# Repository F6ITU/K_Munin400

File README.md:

# K_Munin400
LA2NI's OpenHPSDR 400W HF amplifier (Kicad Version)

This amplifier board is part of a set consisting of a 400 W LD-Mos based RF power amplifier (Munin 400), 
a medium power Zolotarev low pass filter (600 or 1500 W), an Automatic Antenna Tuner (ATU) nickname « Aries » 
and a 4 port antenna switch.

All these developments are the work and intellectual property of Kjell Karlsen LA2NI and Laurence Barker G8NJJ.

This original work can be downloaded from

https://github.com/LA2NI/

https://github.com/laurencebarker

This board was originally developed in December 2021 by Kjell LA2NI , with UltiBoard EDA. This repository is a « bug for bug »
clone of the original amplifier using the Opensource Kicad EDA. 
All these KiCad files are, consequently, the intellectual property of Kjell LA2NI.

This portage (convertion/translation) is placed under the CERN Open source/ Open hardware Licence.

Kicad is an Opensource EDA software maintained by the European Reseach Center CERN (Conseil européen pour la recherche nucléaire)

The original work is protected by the TAPR Open Hardware licence

Munin and Hugin are the two "messenger" ravens of the Norse god Odin - just as Hermes is the messenger-god in Greek mythology, 
and the masterpiece of the OpenHPSDR architecture 

This LDMoS transistor-based amplifier brings speech over the great distances of the "Midgard" of the waves

# Work in progress
do NOT use these files as long as this footnote hasn't been deleted

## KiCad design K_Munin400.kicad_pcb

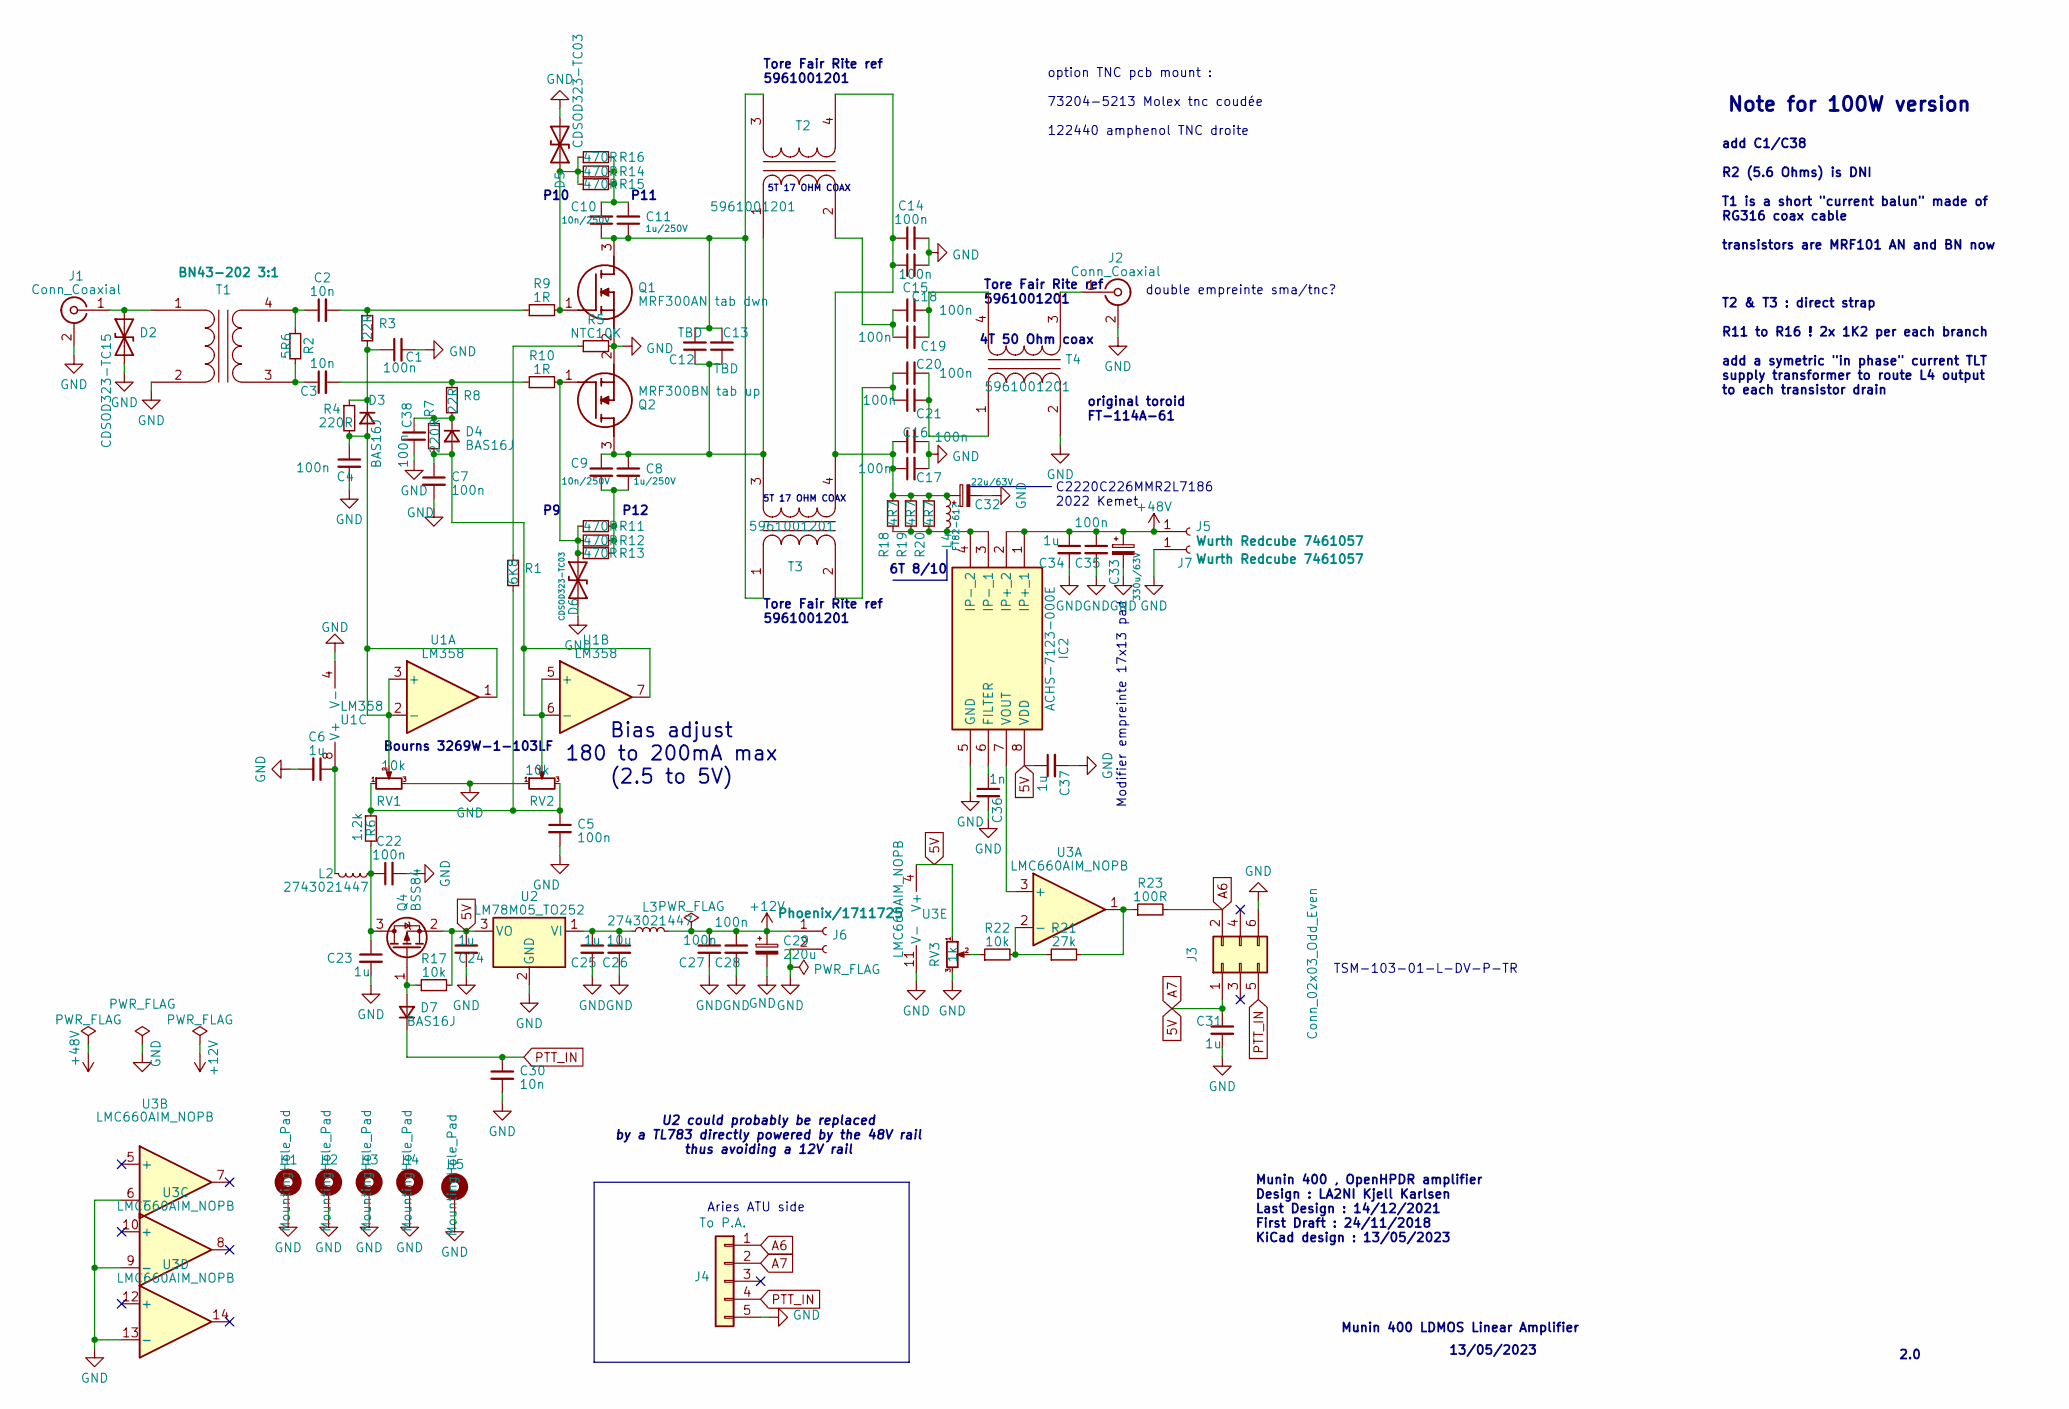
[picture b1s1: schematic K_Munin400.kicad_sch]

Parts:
C1, C38: 100n; C_0805_2012Metric
C2, C3, C30: 10n; C_0805_2012Metric_Pad1.18x1.45mm_HandSolder
C4, C5, C7, C22, C27, C28, C35: 100n; C_0805_2012Metric_Pad1.18x1.45mm_HandSolder
C6, C23, C24, C25, C31, C34, C37: 1u; C_0805_2012Metric_Pad1.18x1.45mm_HandSolder
C8, C11: 1u/250V; C_1812_4532Metric_Pad1.57x3.40mm_HandSolder
C9, C10: 10n/250V; C_1812_4532Metric_Pad1.57x3.40mm_HandSolder
C12, C13: TBD; C_1812_4532Metric_Pad1.57x3.40mm_HandSolder
C14, C15, C16, C17, C18, C19, C20, C21: 100n; C_1812_4532Metric_Pad1.57x3.40mm_HandSolder
C26: 10u; CP_EIA-7343-31_Kemet-D_Pad2.25x2.55mm_HandSolder
C29: 220u; C_Elec_8x10.2
C32: 22u/63V; C_2220_5650Metric_Pad1.97x5.40mm_HandSolder
C33: 330u/63V; CP_Elec_18x17.5
C36: 1n; C_0805_2012Metric_Pad1.18x1.45mm_HandSolder
D2: CDSOD323-TC15; D_SOD-323_HandSoldering
D3, D4, D7: BAS16J; D_SOD-323_HandSoldering
D5, D6: CDSOD323-TC03; D_SOD-323_HandSoldering
H1, H2, H3, H4, H5: MountingHole_Pad; MountingHole_3.5mm_Pad_TopBottom
IC2: ACHS-7123-000E; SOIC-8_3.9x4.9mm_P1.27mm; Mouser Part Number 630-ACHS-7123-000E
J1, J2: Conn_Coaxial; SMA_PINS
J3: Conn_02x03_Odd_Even; IDC-Header_2x03_P2.54mm_Vertical_SMD
J4: To P.A.; Molex_KK-254_AE-6410-05A_1x05_P2.54mm_Vertical
J5, J7: Wurth Redcube 7461057; 7461057
J6: Phoenix/1711725; 1711725
L2, L3: 2743021447; Fair-Rite_2743021447
L4: FT82-61?; T50_V_smd
Q1: MRF300AN tab dwn; TO-247-3_Horizontal_TabDown; Mouser Part Number 771-MRF300AN
Q2: MRF300BN tab up; TO-247-3_Horizontal_TabUp; Mouser Part Number 771-MRF300AN
Q4: BSS84; SOT-23
R1: 6K8; R_0805_2012Metric_Pad1.20x1.40mm_HandSolder
R2: 5R6; R_1812_4532Metric_Pad1.30x3.40mm_HandSolder
R3, R8: 22R; R_0805_2012Metric_Pad1.20x1.40mm_HandSolder
R4, R7: 220R; R_0805_2012Metric_Pad1.20x1.40mm_HandSolder
R5: NTC10K; R_MELF_MMB-0207
R6: 1.2k; R_0805_2012Metric_Pad1.20x1.40mm_HandSolder
R9, R10: 1R; R_0805_2012Metric_Pad1.20x1.40mm_HandSolder
R11, R12, R13, R14, R15, R16: 470R; R_Axial_DIN0414_L11.9mm_D4.5mm_P25.40mm_Horizontal
R17, R22: 10k; R_0805_2012Metric_Pad1.20x1.40mm_HandSolder
R18, R19, R20: 4R7; R_1812_4532Metric_Pad1.30x3.40mm_HandSolder
R21: 27k; R_0805_2012Metric_Pad1.20x1.40mm_HandSolder
R23: 100R; R_0805_2012Metric_Pad1.20x1.40mm_HandSolder
RV1, RV2: 10k; Potentiometer_Bourns_3269W_Vertical
RV3: 1k; Potentiometer_Bourns_3269W_Vertical
T1: BN43-202 3:1; BN43-202
T2: 5961001201; FT114A-61
T3: 5961001201; FT114A-61_B
T4: 5961001201; FT114A-61_out
U1: LM358; SOIC-8_3.9x4.9mm_P1.27mm
U2: LM78M05_TO252; TO-252-2
U3: LMC660AIM_NOPB; SOIC-14_3.9x8.7mm_P1.27mm

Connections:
5V: C24.1, C31.1, C37.1, IC2.8 (VDD), J3.1, J4.2, Q4.2 (S), R17.2, RV3.1, U2.3 (VO), U3.4 (V+)
+12V: C27.1, C28.1, C29.1, J6.1, L3.1
+48V: C33.1, C34.1, C35.1, IC2.1 (IP+_1), IC2.2 (IP+_2), J5.1
A6: J3.2, J4.1, R23.2
GND: C1.2, C4.2, C5.2, C6.2, C7.2, C14.2, C15.2, C16.2, C17.2, C22.2, C23.2, C24.2, C25.2, C26.2, C27.2, C28.2, C29.2, C30.2, C31.2, C32.2, C33.2, C34.2, C35.2, C36.2, C37.2, C38.1, D2.1 (A1), D5.1 (A1), D6.2 (A2), H1.1, H2.1, H3.1, H4.1, H5.1, IC2.5 (GND), J1.2 (Ext), J2.2 (Ext), J3.6, J4.5, J6.2, J7.1, Q1.2 (S), Q2.2 (S), R5.2, RV1.3, RV2.1, RV3.3, T1.2 (AB), T4.2 (AB), U1.4 (V-), U2.2 (GND), U3.6 (-), U3.9 (-), U3.11 (V-), U3.13 (-)
unnamed: C2.2, R3.1, R9.1
unnamed: C3.2, R8.1, R10.1
unnamed: C5.1, R1.1, R6.1, RV1.1, RV2.3
unnamed: C8.2, C9.2, R11.2, R12.2, R13.2
unnamed: C10.2, C11.2, R14.2, R15.2, R16.2
unnamed: D2.2 (A2), J1.1 (In), T1.1 (AA)
unnamed: C4.1, D3.2 (A), R4.2, RV1.2, U1.1, U1.2 (-), U1.3 (+)
unnamed: C1.1, D3.1 (K), R3.2, R4.1
unnamed: C7.1, D4.2 (A), R7.2, RV2.2, U1.5 (+), U1.6 (-), U1.7
unnamed: C38.2, D4.1 (K), R7.1, R8.2
unnamed: D5.2 (A2), Q1.1 (G), R9.2, R14.1, R15.1, R16.1
unnamed: D6.1 (A1), Q2.1 (G), R10.2, R11.1, R12.1, R13.1
unnamed: D7.2 (A), Q4.1 (G), R17.1
unnamed: C36.1, IC2.6 (FILTER)
unnamed: IC2.3 (IP-_1), IC2.4 (IP-_2), L4.1, R18.2, R19.2, R20.2
unnamed: IC2.7 (VOUT), U3.3 (+)
unnamed: J2.1 (In), T4.3 (SA)
unnamed: C10.1, C11.1, C12.2, C13.2, Q1.3 (D), T2.3 (SB), T3.1 (AA)
unnamed: C8.1, C9.1, C12.1, C13.1, Q2.3 (D), T2.1 (AA), T3.3 (SB)
unnamed: C22.1, C23.1, L2.2, Q4.3 (D), R6.2
unnamed: R1.2, R5.1
unnamed: R21.2, R23.1, U3.1
unnamed: R22.1, RV3.2
unnamed: C3.1, R2.2, T1.3 (SA)
unnamed: C2.1, R2.1, T1.4 (SB)
unnamed: C18.1, C19.1, T2.2 (AB)
unnamed: C14.1, C15.1, C16.1, C17.1, C32.1, L4.2, R18.1, R19.1, R20.1, T2.4 (SA), T3.4 (SA)
unnamed: C20.1, C21.1, T3.2 (AB)
unnamed: C20.2, C21.2, T4.1 (AA)
unnamed: C18.2, C19.2, T4.4 (SB)
unnamed: C6.1, L2.1, U1.8 (V+)
unnamed: C25.1, C26.1, L3.2, U2.1 (VI)
unnamed: R21.1, R22.2, U3.2 (-)
PTT_IN: C30.1, D7.1 (K), J3.5, J4.4

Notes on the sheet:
5T 17 OHM COAX
Note for 100W version
Modifier empreinte 17x13 pad
Aries ATU side
13/05/2023
Munin 400 , OpenHPDR amplifier Design : LA2NI Kjell Karlsen Last Design : 14/12/2021 First Draft : 24/11/2018 KiCad design : 13/05/2023
2.0
TSM-103-01-L-DV-P-TR
Bourns 3269W-1-103LF
Munin 400 LDMOS Linear Amplifier
P9 P12
U2 could probably be replaced by a TL783 directly powered by the 48V rail thus avoiding a 12V rail
6T 8/10
Tore Fair Rite ref 5961001201
option TNC pcb mount : 73204-5213 Molex tnc coudée 122440 amphenol TNC droite
Bias adjust 180 to 200mA max (2.5 to 5V)
P10 P11
double empreinte sma/tnc?
4T 50 Ohm coax
original toroid FT-114A-61
add C1/C38 R2 (5.6 Ohms) is DNI T1 is a short "current balun" made of RG316 coax cable transistors are MRF101 AN and BN now T2 & T3 : direct strap R11 to R16 ! 2x 1K2 per each branch add a symetric "in phase" current TLT supply transformer to route L4 output to each transistor drain
C2220C226MMR2L7186 2022 Kemet

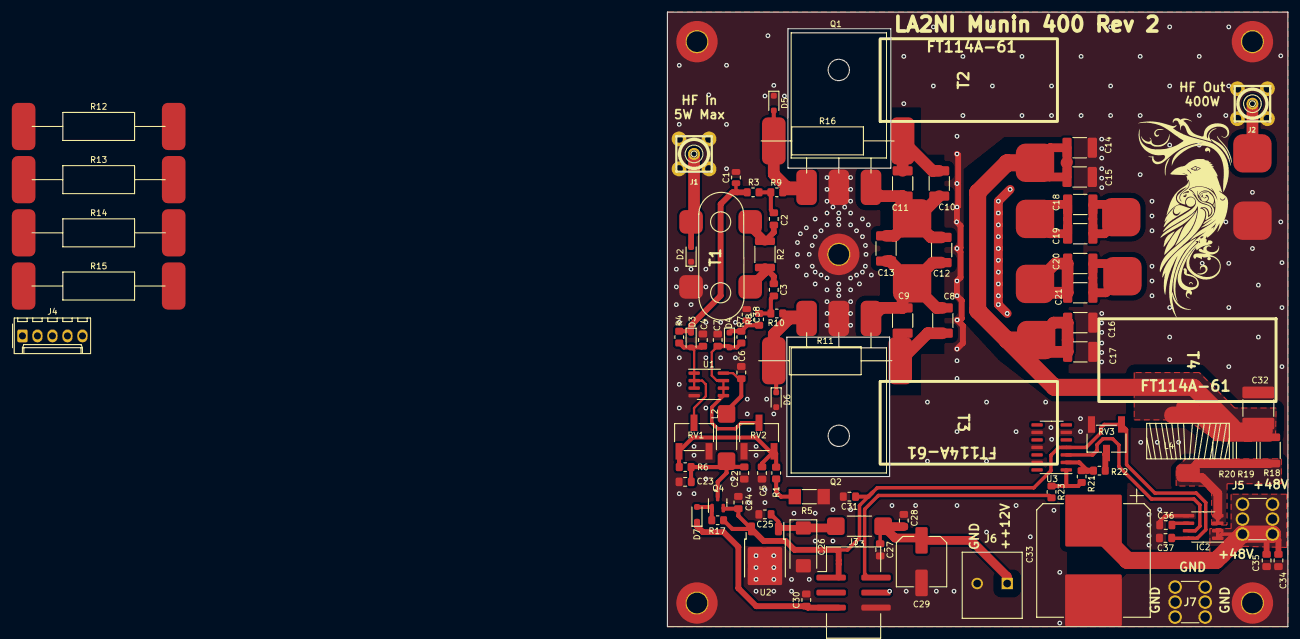
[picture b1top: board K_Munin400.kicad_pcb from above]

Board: 2 copper layers, 105.0 x 104.0 mm, 96 parts (0 on the bottom side), 39 nets.

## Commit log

2023-05-11 first commit, repository creation
2023-05-12 schematic early stage
2023-05-12 new README
2023-05-13 schematic completed, footprints not yet defined
2023-05-13 schematic completed, footprint not yet configured
2023-05-22 all footprint and 3D module defined, schematic completed
2023-05-23 3Dshapes set
2023-05-25 some debuging, new placement, silk logo
2023-05-25 placement and routing completed
2023-05-25 new gerber, small pcb mods
2023-05-25 new readme, new picture
2026-03-23 kicad 10 update, minor schematic changes
